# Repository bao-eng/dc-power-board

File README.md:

# dc-power-board
9-36V DC input 5.1V/5A output board for Raspberry Pi

## Features
- 9-36V DC input
- 5.1V/5A output(sufficient to power Raspberry Pi5)
- Reverse polarity protection
- INA226 current, voltage and power monitor
- EEPROM for board identification

## EEPROM
### eep file preparation
```eepmake ./dc_power_board_v1_eeprom.txt dc_power_board_v1.eep```
### EEPROM flashing
Short TP1 and TP2 or short R24 to disable EEPROM write protection. \
Run: ```sudo eepflash.sh -w -f=dc_power_board_v1.eep -t=24c32 -a=53```

## Device tree overlay
### Device tree overlay compilation
```dtc -@ -Hepapr -I dts -O dtb -o dc-power-board-v1.dtbo dc-power-board-v1.dts```

### dtbo installation
Copy ```dc-power-board-v1.dtbo``` to the ```/boot/overlays/``` directory.

## Power monitor usage
### Get current in mA
```cat /sys/devices/platform/soc/fe804000.i2c/i2c-1/1-0045/hwmon/hwmon2/curr1_input```

### Get voltage in mV
```cat /sys/devices/platform/soc/fe804000.i2c/i2c-1/1-0045/hwmon/hwmon2/in1_input```

### Get power in mW
```cat /sys/devices/platform/soc/fe804000.i2c/i2c-1/1-0045/hwmon/hwmon2/power1_input```

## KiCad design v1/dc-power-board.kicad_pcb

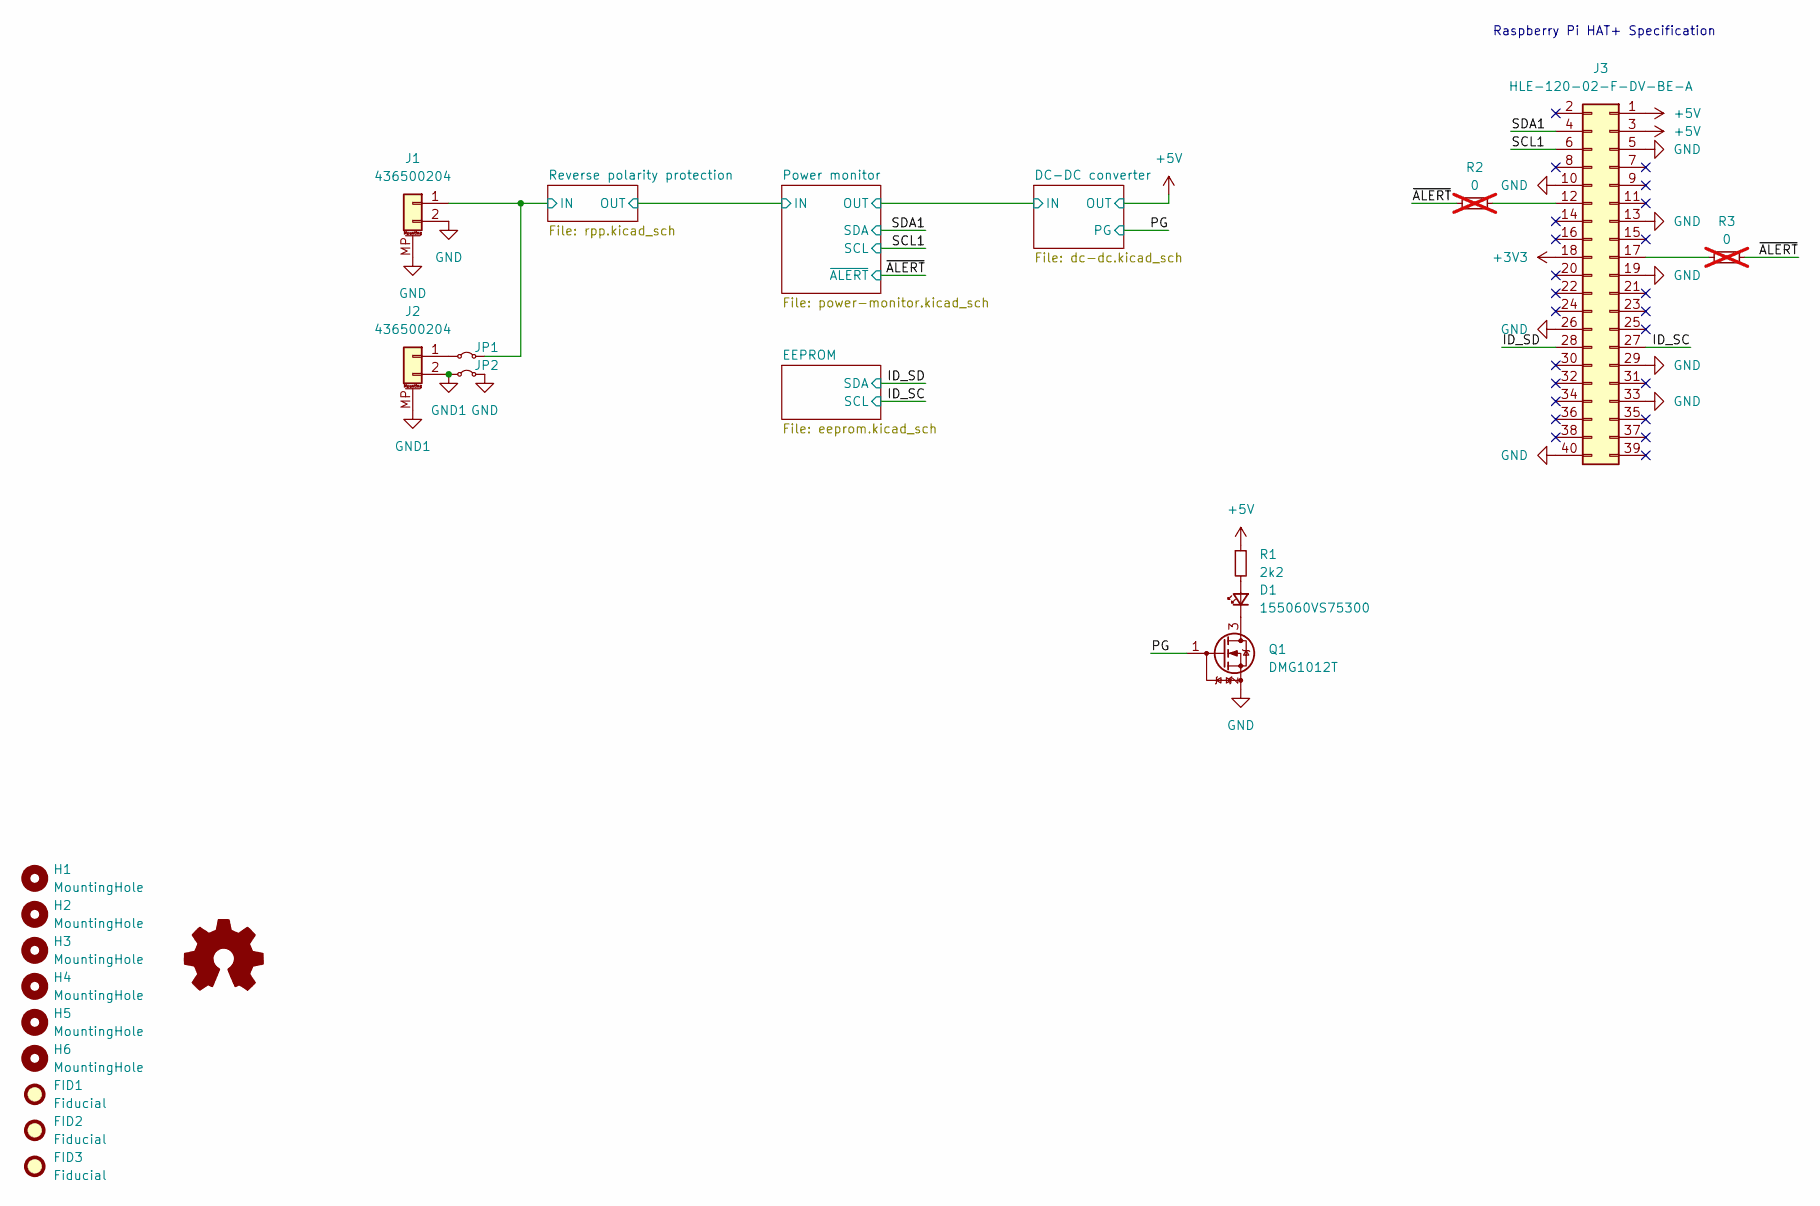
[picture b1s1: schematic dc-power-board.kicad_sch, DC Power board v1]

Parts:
D1: 155060VS75300; LED_0603_1608Metric
FID1, FID2, FID3: Fiducial; Fiducial_1.5mm_Mask3mm
H1, H2, H3, H4, H5, H6: MountingHole; MountingHole_2.75mm_M2.5
J1, J2: 436500204
J3: HLE-120-02-F-DV-BE-A; Samtec_HLE-120-02-xxx-DV-BE-A_2x20_P2.54mm_Horizontal
JP1, JP2: 0; HARWIN_S1911-46R; MPN S1911-46R
Q1: DMG1012T; SOT-523
R1: 2k2; R_0402_1005Metric; MPN RC0402FR-072K2L
R2, R3: 0; R_0402_1005Metric; MPN RC0402JR-070RL; not fitted
SYM1: Logo_Open_Hardware_Small; OSHW-Logo_5.7x6mm_SilkScreen

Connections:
+3V3: J3.18; also elsewhere on the board
+5V: J3.1, J3.3, R1.1; also elsewhere on the board
/ID_SC: J3.27; also elsewhere on the board
/ID_SD: J3.28; also elsewhere on the board
/PG: Q1.1 (G); also elsewhere on the board
/Reverse polarity protection/IN: J1.1, JP1.2 (B); also elsewhere on the board
/SCL1: J3.6; also elsewhere on the board
/SDA1: J3.4; also elsewhere on the board
/~ALERT: R2.1, R3.2; also elsewhere on the board
GND: J1.2, J1.MP (MountPin), J3.5, J3.10, J3.13, J3.19, J3.26, J3.29, J3.33, J3.40, JP2.2 (B), Q1.2 (S); also elsewhere on the board
GND1: J2.2, J2.MP (MountPin), JP2.1 (A)
unnamed: D1.2 (A), R1.2
unnamed: D1.1 (K), Q1.3 (D)
unnamed: J2.1, JP1.1 (A)
unnamed: J3.12, R2.2
unnamed: J3.17, R3.1

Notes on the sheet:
Raspberry Pi HAT+ Specification

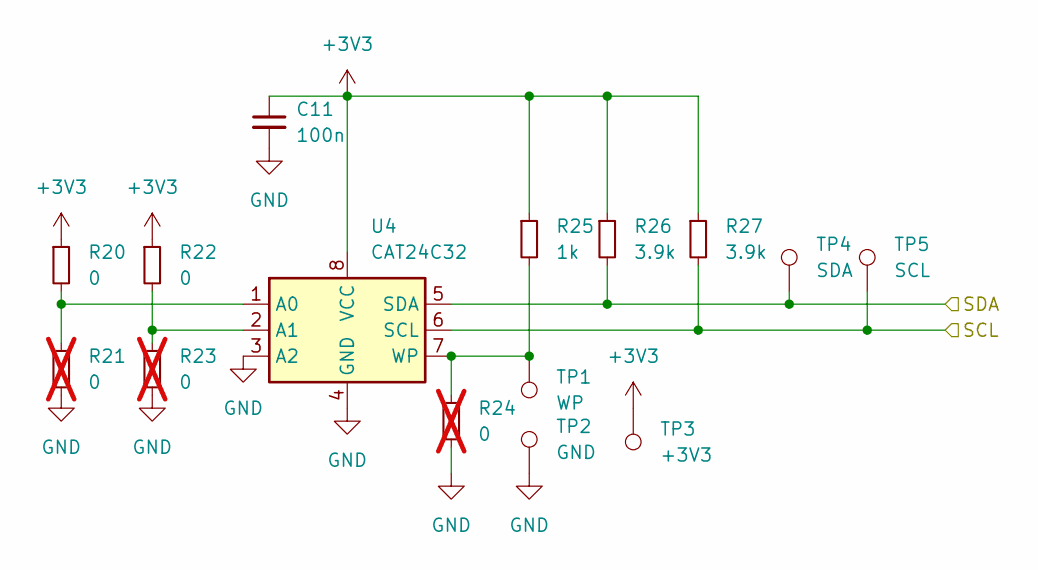
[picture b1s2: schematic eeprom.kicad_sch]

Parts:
C11: 100n; C_0402_1005Metric; MPN 885012105001
R20, R22: 0; R_0402_1005Metric; MPN RC0402FR-071KL
R21, R23, R24: 0; R_0402_1005Metric; MPN RC0402FR-071KL; not fitted
R25: 1k; R_0402_1005Metric; MPN RC0402FR-071KL
R26, R27: 3.9k; R_0402_1005Metric; MPN RC0402FR-073K9L
TP1: WP; TestPoint_Pad_D2.0mm
TP2: GND; TestPoint_Pad_D2.0mm
TP3: +3V3; TestPoint_Pad_D2.0mm
TP4: SDA; TestPoint_Pad_D2.0mm
TP5: SCL; TestPoint_Pad_D2.0mm
U4: CAT24C32; TSSOP-8_4.4x3mm_P0.65mm; MPN CAT24C32YI-GT3

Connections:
+3V3: C11.1, R20.1, R22.1, R25.1, R26.1, R27.1, TP3.1, U4.8 (VCC); also elsewhere on the board
/ID_SC: R27.2, TP5.1, U4.6 (SCL); also elsewhere on the board
/ID_SD: R26.2, TP4.1, U4.5 (SDA); also elsewhere on the board
GND: C11.2, R21.2, R23.2, R24.2, TP2.1, U4.3 (A2), U4.4 (GND); also elsewhere on the board
unnamed: R20.2, R21.1, U4.1 (A0)
unnamed: R22.2, R23.1, U4.2 (A1)
unnamed: R24.1, R25.2, TP1.1, U4.7 (WP)

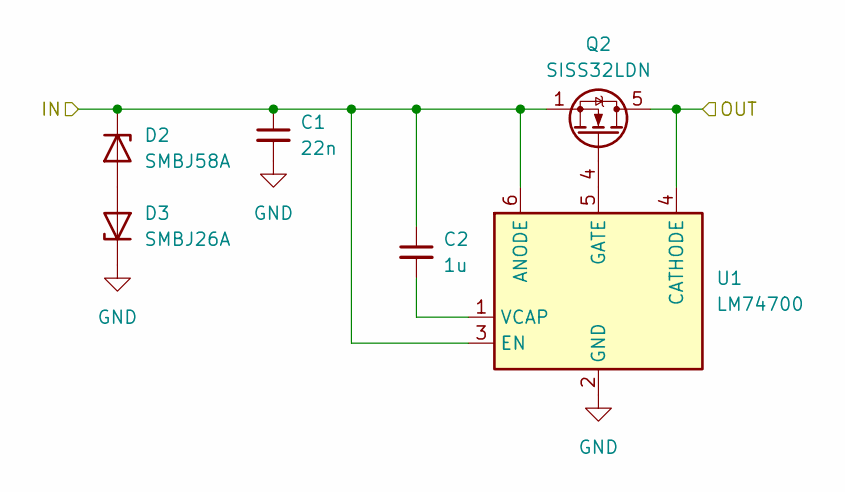
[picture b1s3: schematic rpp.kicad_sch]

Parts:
C1: 22n; C_0402_1005Metric; MPN GRM155R71H223KA12D
C2: 1u; C_0603_1608Metric; MPN CGA3E1X7R1E105K080AD
D2: SMBJ58A; D_SMB
D3: SMBJ26A; D_SMB
Q2: SISS32LDN; Vishay_PowerPAK_1212-8_Single
U1: LM74700; SOT-23-6; MPN LM74700QDBVRQ1

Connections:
/Power monitor/IN: Q2.5 (D), U1.4 (CATHODE); also elsewhere on the board
/Reverse polarity protection/IN: C1.1, C2.1, D2.1 (K), Q2.1 (S), Q2.2 (S), Q2.3 (S), U1.3 (EN), U1.6 (ANODE); also elsewhere on the board
GND: C1.2, D3.1 (K), U1.2 (GND); also elsewhere on the board
unnamed: D2.2 (A), D3.2 (A)
unnamed: Q2.4 (G), U1.5 (GATE)
unnamed: C2.2, U1.1 (VCAP)

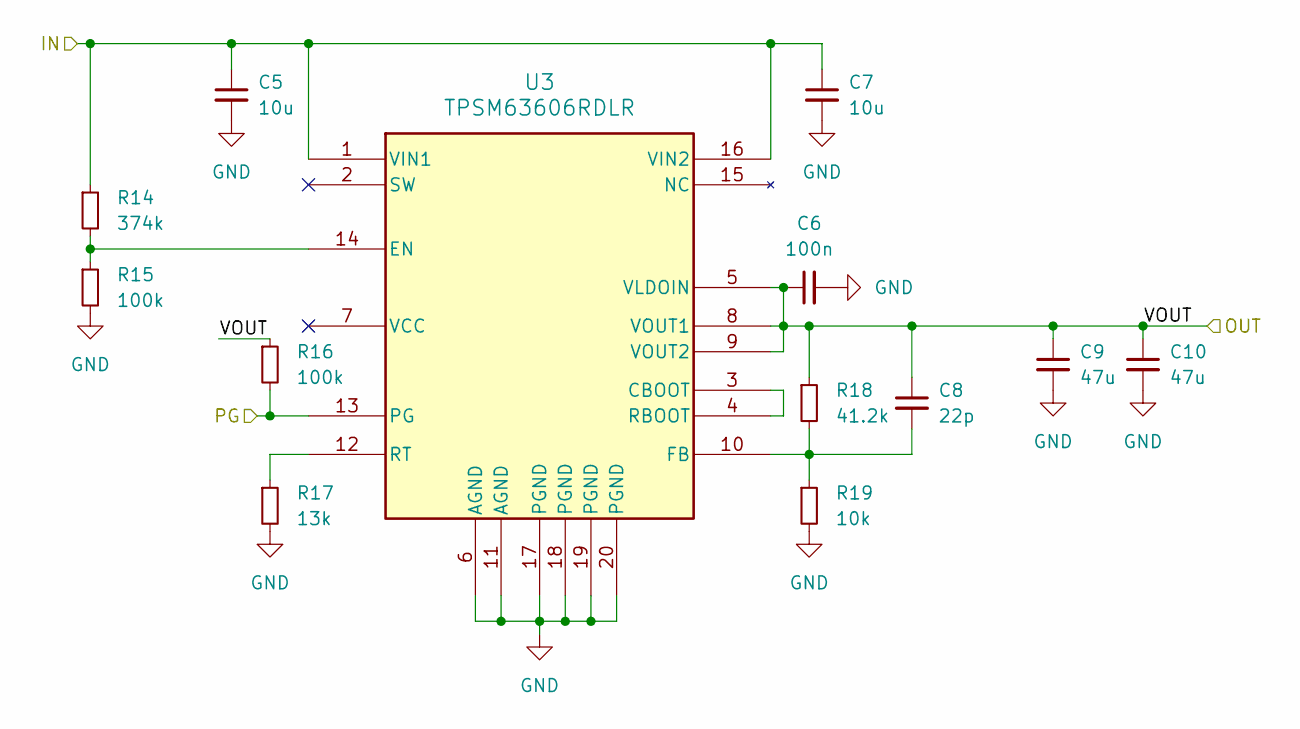
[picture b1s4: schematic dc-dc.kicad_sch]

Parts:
C5, C7: 10u; C_1210_3225Metric; MPN CNA6P1X7R1H106K
C6: 100n; C_0402_1005Metric; MPN 885012105001
C8: 22p; C_0402_1005Metric; MPN GRM1555C1H220JA01D
C9, C10: 47u; C_1210_3225Metric; MPN GRM32ER71A476ME15L
R14: 374k; R_0402_1005Metric; MPN RC0402FR-07374KL
R15, R16: 100k; R_0402_1005Metric; MPN RC0402FR-07100KL
R17: 13k; R_0402_1005Metric; MPN RC0402FR-0713KL
R18: 41.2k; R_0402_1005Metric; MPN RC0402FR-1341K2L
R19: 10k; R_0402_1005Metric; MPN RC0402JR-0710KL
U3: TPSM63606RDLR; B3QFN20_RDL_TEX

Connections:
+5V: C6.1, C8.1, C9.1, C10.1, R16.1, R18.1, U3.5 (VLDOIN), U3.8 (VOUT1), U3.9 (VOUT2); also elsewhere on the board
/DC-DC converter/IN: C5.1, C7.1, R14.1, U3.1 (VIN1), U3.16 (VIN2); also elsewhere on the board
/PG: R16.2, U3.13 (PG); also elsewhere on the board
GND: C5.2, C6.2, C7.2, C9.2, C10.2, R15.2, R17.2, R19.2, U3.6 (AGND), U3.11 (AGND), U3.17 (PGND), U3.18 (PGND), U3.19 (PGND), U3.20 (PGND); also elsewhere on the board
unnamed: U3.3 (CBOOT), U3.4 (RBOOT)
unnamed: R14.2, R15.1, U3.14 (EN)
unnamed: C8.2, R18.2, R19.1, U3.10 (FB)
unnamed: R17.1, U3.12 (RT)

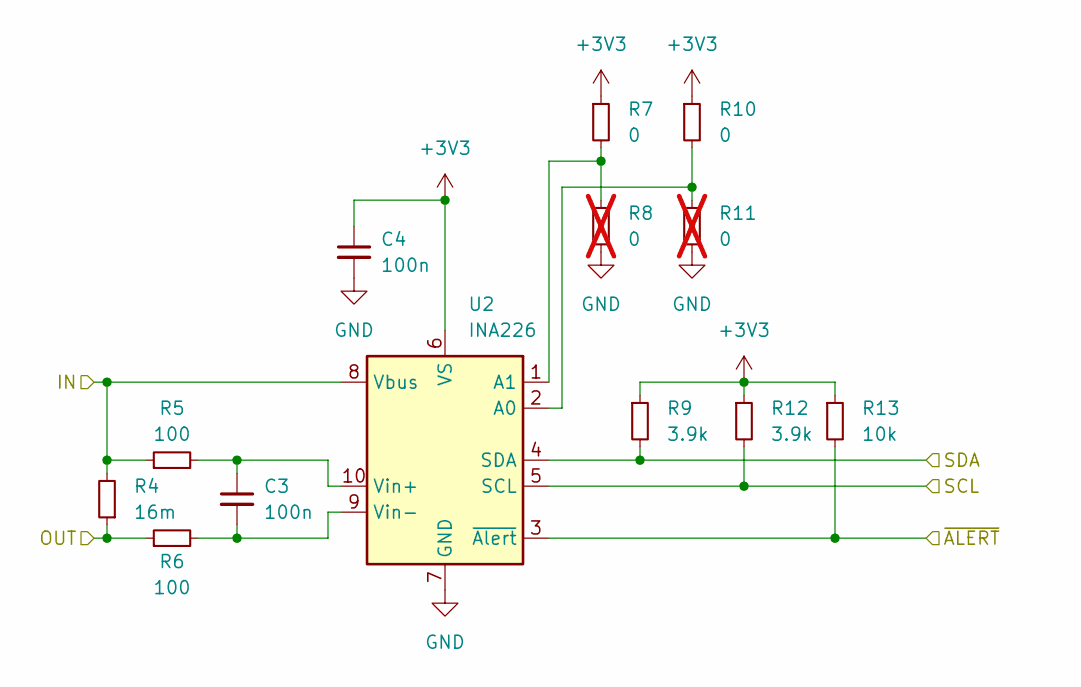
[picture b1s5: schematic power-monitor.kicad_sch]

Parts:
C3, C4: 100n; C_0402_1005Metric; MPN 885012105001
R4: 16m; R_Shunt_Vishay_WPC2512_6332Metric_R001~R056; MPN WPC2512QLR016FYR
R5, R6: 100; R_0402_1005Metric; MPN RT0402BRD07100RL
R7, R10: 0; R_0402_1005Metric; MPN RC0402JR-070RL
R8, R11: 0; R_0402_1005Metric; MPN RC0402JR-070RL; not fitted
R9, R12: 3.9k; R_0402_1005Metric; MPN RC0402FR-073K9L
R13: 10k; R_0402_1005Metric; MPN RC0402JR-0710KL
U2: INA226; VSSOP-10_3x3mm_P0.5mm

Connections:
+3V3: C4.1, R7.1, R9.1, R10.1, R12.1, R13.1, U2.6 (VS); also elsewhere on the board
/DC-DC converter/IN: R4.1, R6.1; also elsewhere on the board
/Power monitor/IN: R4.2, R5.1, U2.8 (Vbus); also elsewhere on the board
/SCL1: R12.2, U2.5 (SCL); also elsewhere on the board
/SDA1: R9.2, U2.4 (SDA); also elsewhere on the board
/~ALERT: R13.2, U2.3 (~Alert); also elsewhere on the board
GND: C4.2, R8.2, R11.2, U2.7 (GND); also elsewhere on the board
unnamed: R10.2, R11.1, U2.2 (A0)
unnamed: R7.2, R8.1, U2.1 (A1)
unnamed: C3.1, R5.2, U2.10 (Vin+)
unnamed: C3.2, R6.2, U2.9 (Vin-)

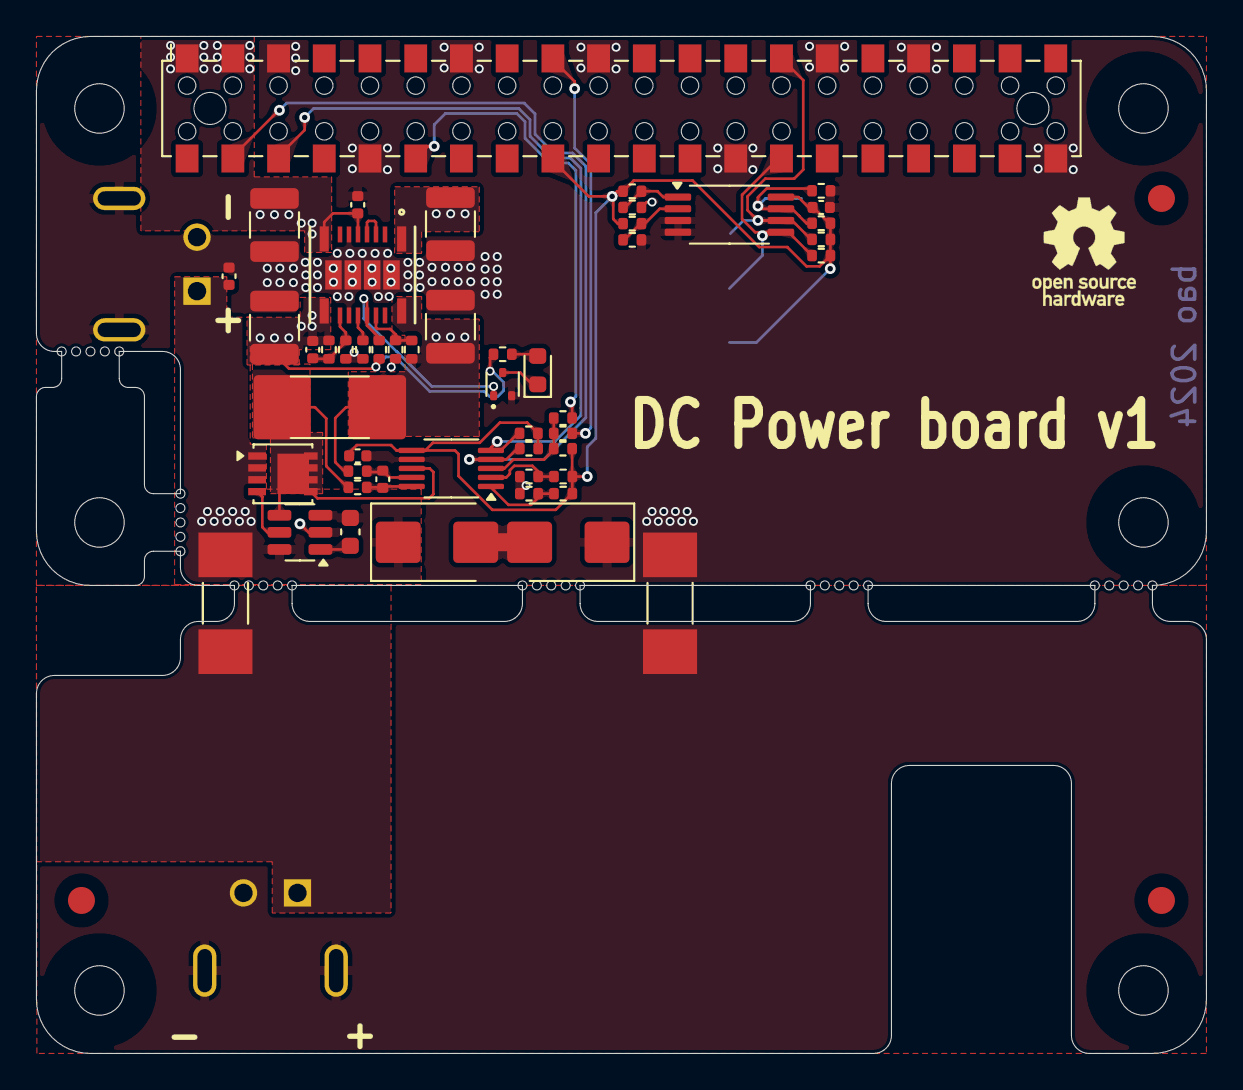
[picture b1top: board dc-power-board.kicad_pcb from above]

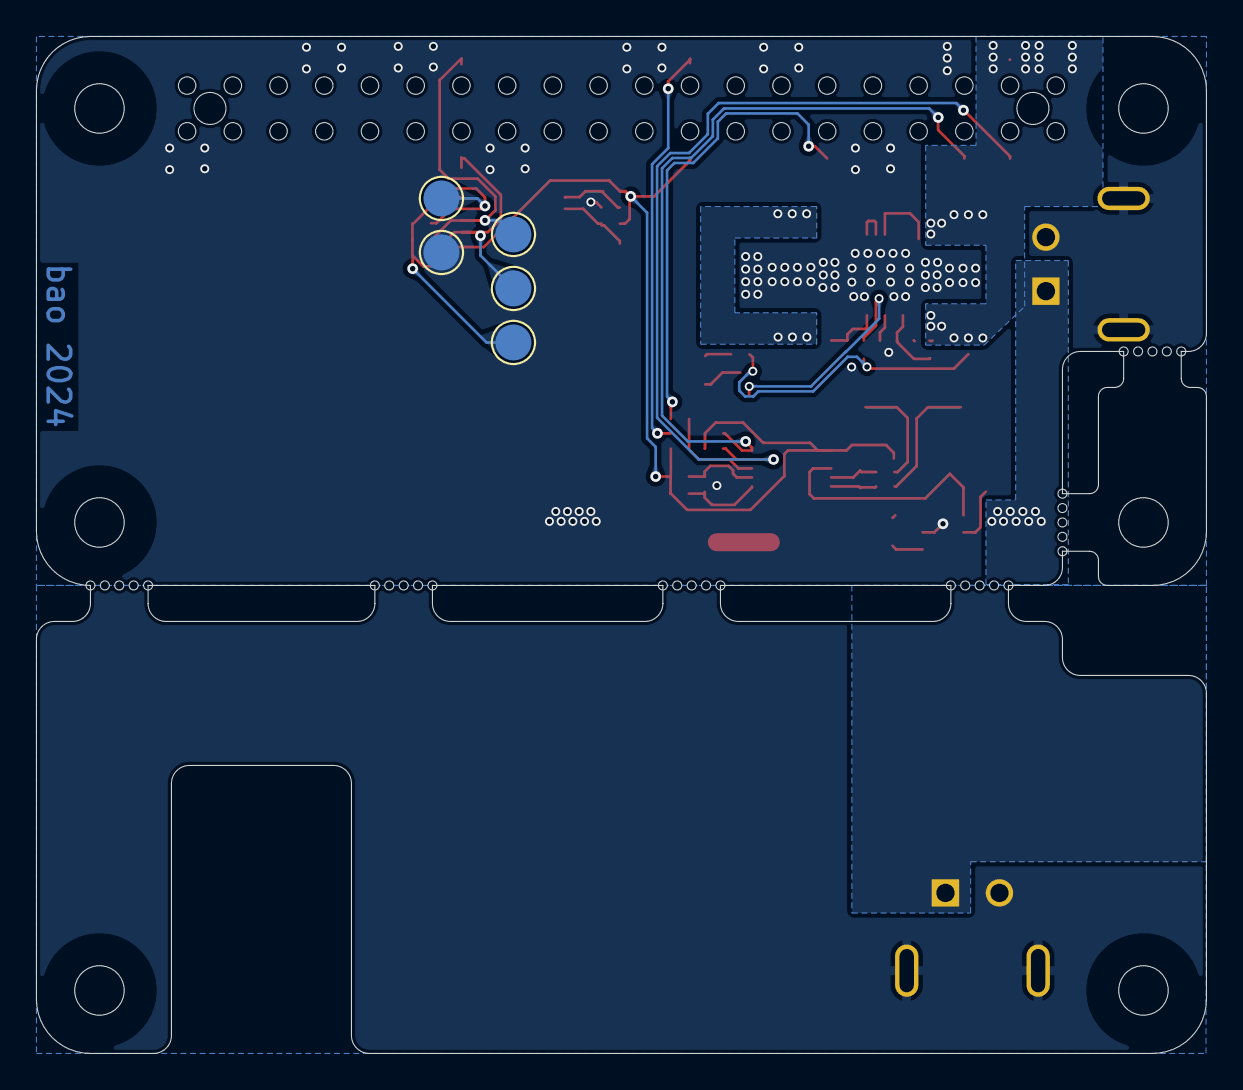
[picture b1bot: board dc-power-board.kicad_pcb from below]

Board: 2 copper layers, 65.0 x 56.5 mm, 67 parts (5 on the bottom side), 32 nets.
